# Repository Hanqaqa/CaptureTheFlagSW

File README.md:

# CaptureTheFlag
Capture the Flag for Arduino with 2 OLED Screens and RFID (Work in Progress)

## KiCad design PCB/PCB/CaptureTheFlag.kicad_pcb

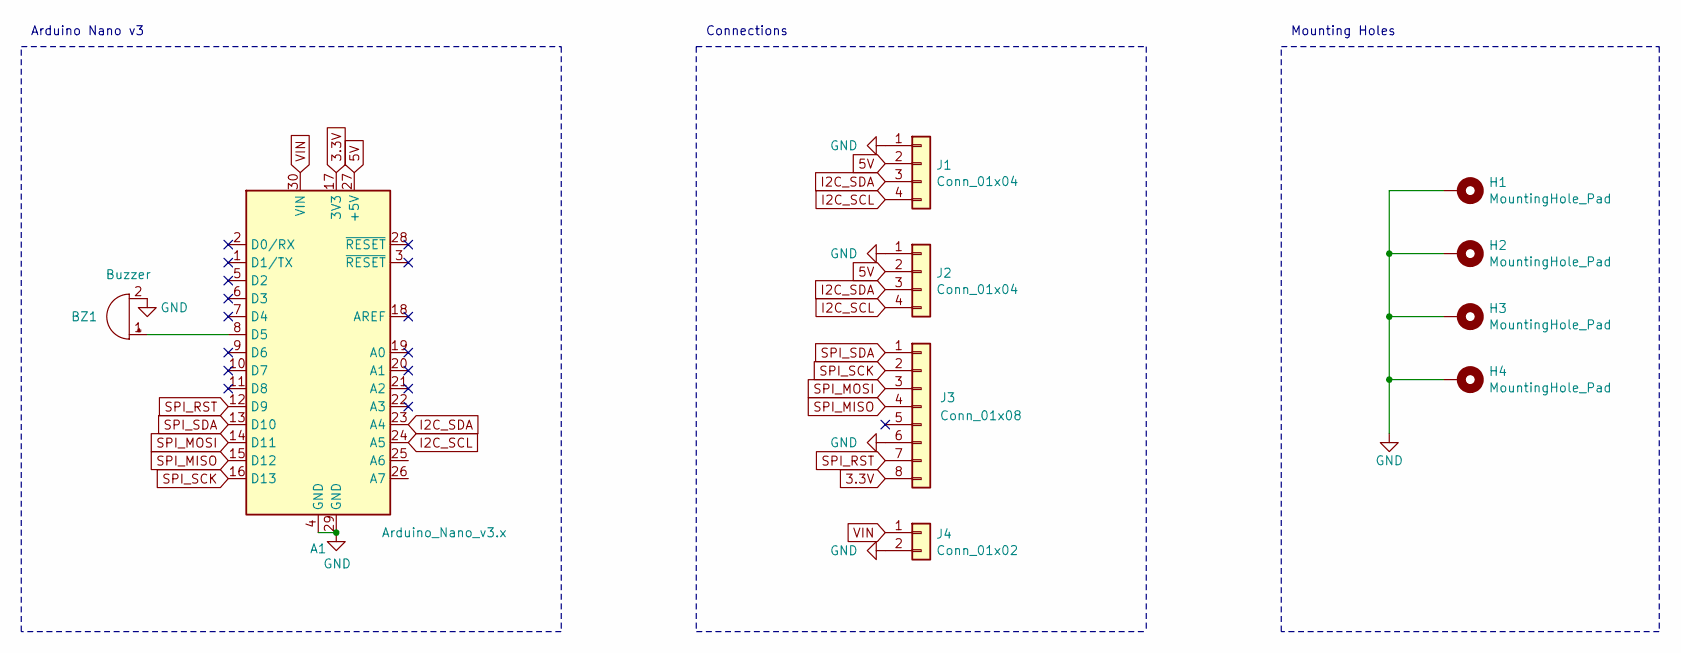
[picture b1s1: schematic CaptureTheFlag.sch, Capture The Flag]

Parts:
A1: Arduino_Nano_v3.x; Arduino_Nano_WithMountingHoles
BZ1: Buzzer; Buzzer_12x9.5RM7.6
H1, H2, H3, H4: MountingHole_Pad; MountingHole_3.2mm_M3_Pad_Via
J1, J2: Conn_01x04; PinHeader_1x04_P2.54mm_Vertical
J3: Conn_01x08; PinHeader_1x08_P2.54mm_Vertical
J4: Conn_01x02; PinHeader_1x02_P2.54mm_Vertical

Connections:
3.3V: A1.17 (3V3), J3.8
5V: A1.27 (+5V), J1.2, J2.2
GND: A1.4 (GND), A1.29 (GND), BZ1.2 (+), H1.1, H2.1, H3.1, H4.1, J1.1, J2.1, J3.6, J4.2
I2C_SCL: A1.24 (A5), J1.4, J2.4
I2C_SDA: A1.23 (A4), J1.3, J2.3
unnamed: A1.8 (D5), BZ1.1 (-)
SPI_MISO: A1.15 (D12), J3.4
SPI_MOSI: A1.14 (D11), J3.3
SPI_RST: A1.12 (D9), J3.7
SPI_SCK: A1.16 (D13), J3.2
SPI_SDA: A1.13 (D10), J3.1
VIN: A1.30 (VIN), J4.1

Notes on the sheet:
Arduino Nano v3
Connections
Mounting Holes

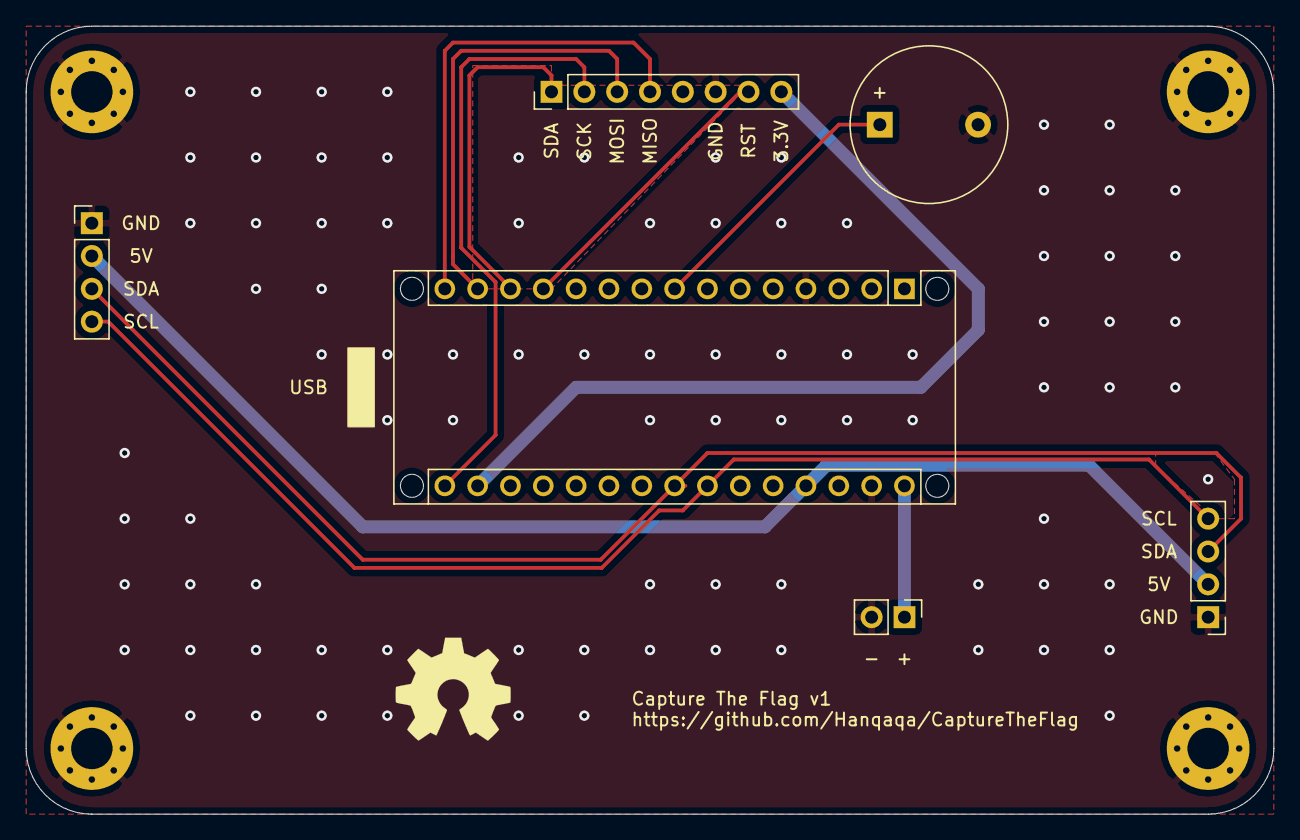
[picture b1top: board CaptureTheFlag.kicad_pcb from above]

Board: 2 copper layers, 96.5 x 61.0 mm, 10 parts (0 on the bottom side), 12 nets.

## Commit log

2021-04-30 v1.5
2021-06-01 Errors correct
2021-06-01 Baudios
2021-06-01 Errors
2021-06-01 Buzzer
